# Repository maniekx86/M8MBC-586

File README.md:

# M8MBC-586

Open-source Pentium motherboard with an FPGA chipset - hardware repository

Work in progress...

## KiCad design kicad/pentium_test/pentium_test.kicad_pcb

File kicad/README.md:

# M8MBC-586 KiCad source

KiCad schematics and PCB design of the M8MBC-586 project. Not production ready (as time of writing the design is being checked)

## Credits
- Socket 7 symbol & footprint - Rigo (0xCats) - https://github.com/rigred/kicad-retro/
- CPU VRM - Necroware - https://github.com/necroware/s7-vrm

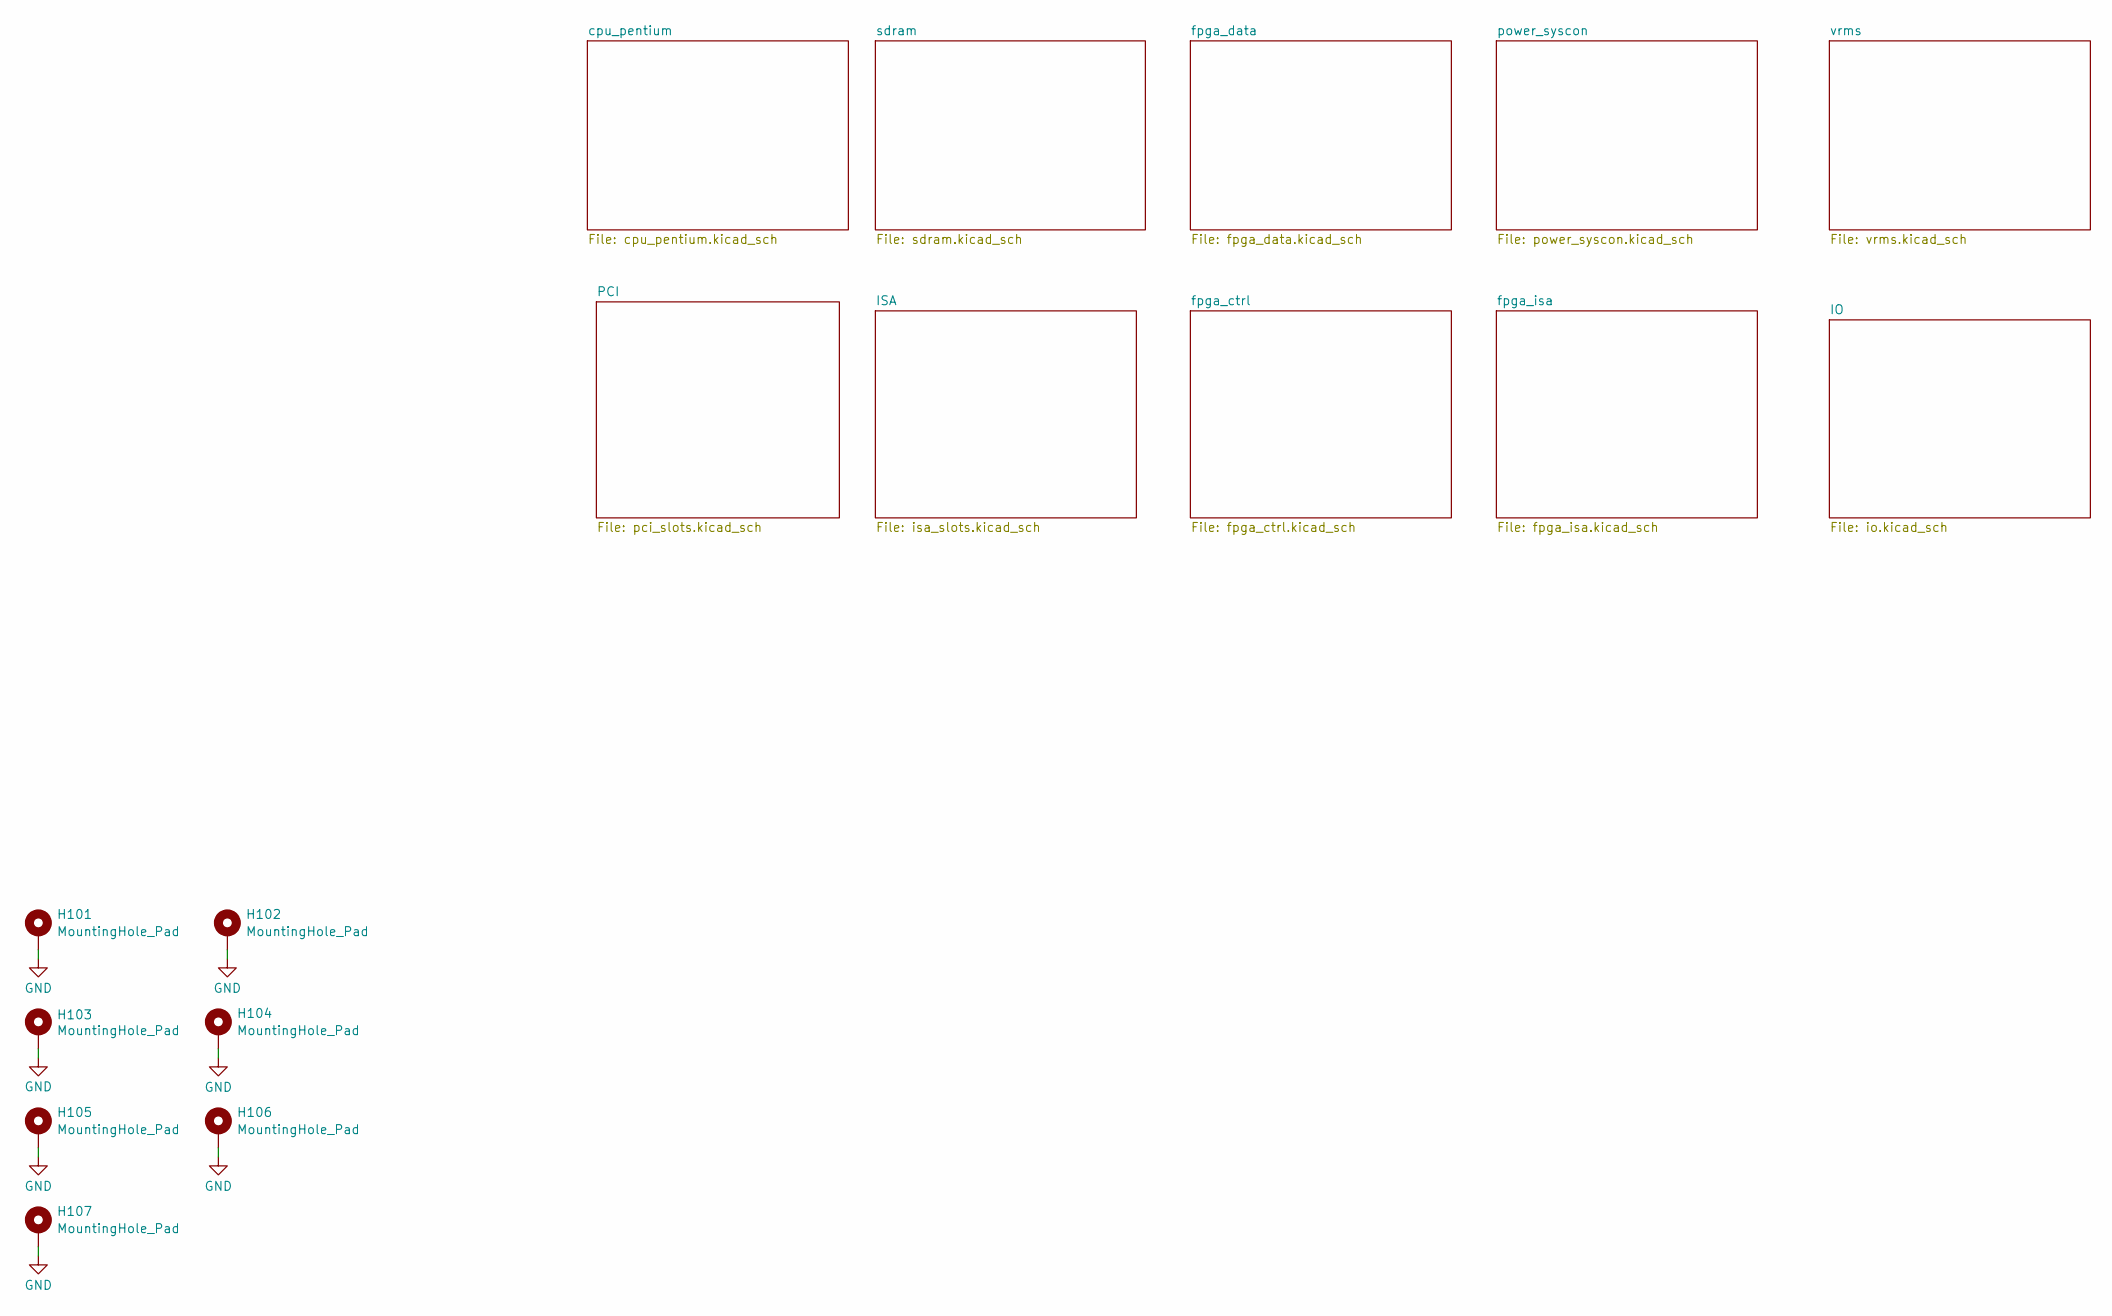
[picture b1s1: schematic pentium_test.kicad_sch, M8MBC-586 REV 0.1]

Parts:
H101, H102, H103, H104, H105, H106, H107: MountingHole_Pad; MountingHole_4.3mm_M4_Pad_Via

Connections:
GND: H101.1, H102.1, H103.1, H104.1, H105.1, H106.1, H107.1; also elsewhere on the board

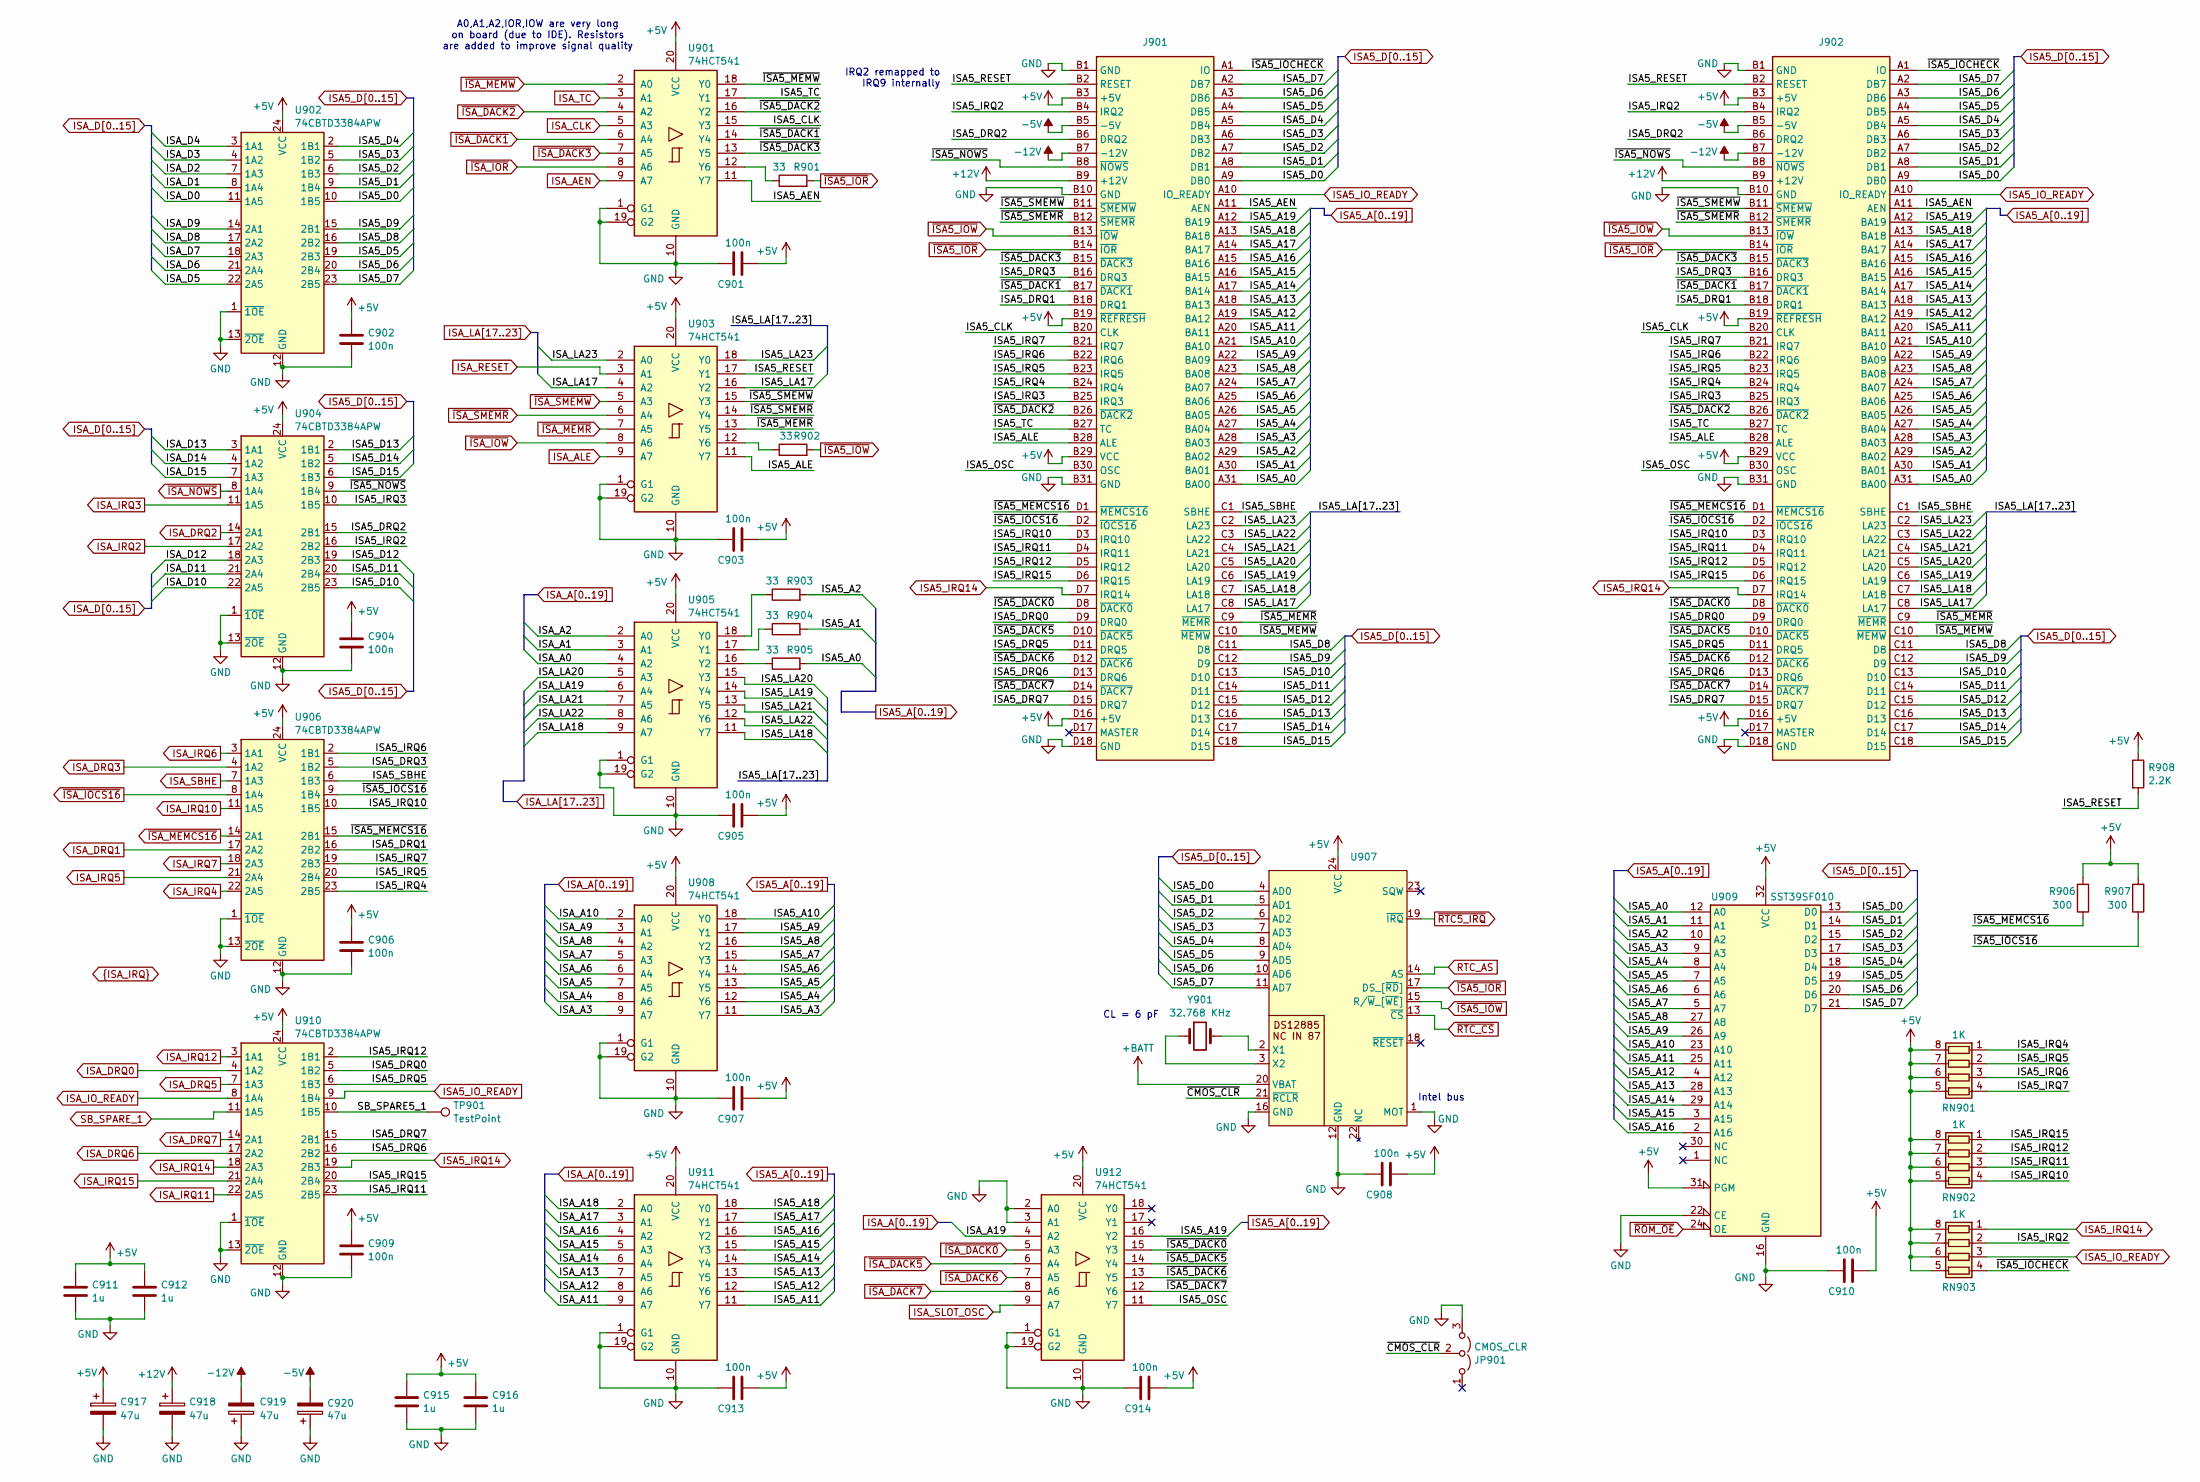
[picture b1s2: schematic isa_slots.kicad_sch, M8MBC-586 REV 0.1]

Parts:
C901, C902, C903, C904, C905, C906, C907, C908, C909, C910, C913, C914: 100n; C_0603_1608Metric
C911, C912, C915, C916: 1u; C_0805_2012Metric
C917, C918, C919, C920: 47u; CP_Radial_D5.0mm_P2.50mm
J901, J902: TE_7-5530843-0
JP901: CMOS_CLR; PinHeader_1x03_P2.54mm_Vertical
R901, R902, R903, R904, R905: 33; R_0603_1608Metric
R906, R907: 300; R_0603_1608Metric
R908: 2.2K; R_0603_1608Metric
RN901, RN902, RN903: 1K; R_Array_Convex_4x0603
TP901: TestPoint; TestPoint_Pad_D1.0mm
U901, U903, U905, U908, U911, U912: 74HCT541; TSSOP-20_4.4x6.5mm_P0.65mm
U902, U904, U906, U910: 74CBTD3384APW; TSSOP-24_4.4x7.8mm_P0.65mm
U907: DIP-24_W15.24mm_Socket
U909: SST39SF010; DIP-32_W15.24mm_Socket
Y901: 32.768 KHz; Crystal_C38-LF_D3.0mm_L8.0mm_Horizontal

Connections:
+5V: C901.2, C902.1, C903.2, C904.1, C905.2, C906.1, C907.2, C908.2, C909.1, C910.2, C911.1, C912.1, C913.2, C914.2, C915.1, C916.1, C917.1, J901.B3 (+5V), J901.B19 (~REFRESH), J901.B29 (VCC), J901.D16 (+5V), J902.B3 (+5V), J902.B19 (~REFRESH), J902.B29 (VCC), J902.D16 (+5V), R906.2, R907.2, R908.1, RN901.5 (R4.2), RN901.6 (R3.2), RN901.7 (R2.2), RN901.8 (R1.2), RN902.5 (R4.2), RN902.6 (R3.2), RN902.7 (R2.2), RN902.8 (R1.2), RN903.5 (R4.2), RN903.6 (R3.2), RN903.7 (R2.2), RN903.8 (R1.2), U901.20 (VCC), U902.24 (VCC), U903.20 (VCC), U904.24 (VCC), U905.20 (VCC), U906.24 (VCC), U907.24 (VCC), U908.20 (VCC), U909.31 (PGM), U909.32 (VCC), U910.24 (VCC), U911.20 (VCC), U912.20 (VCC); also elsewhere on the board
+12V: C918.1, J901.B9 (+12V), J902.B9 (+12V); also elsewhere on the board
+BATT: U907.20 (VBAT); also elsewhere on the board
-5V: C920.2, J901.B5 (-5V), J902.B5 (-5V); also elsewhere on the board
-12V: C919.2, J901.B7 (-12V), J902.B7 (-12V); also elsewhere on the board
/ISA/ISA5_AEN: J901.A11 (AEN), J902.A11 (AEN), U901.11 (Y7)
/ISA/ISA5_ALE: J901.B28 (ALE), J902.B28 (ALE), U903.11 (Y7)
/ISA/ISA5_CLK: J901.B20 (CLK), J902.B20 (CLK), U901.15 (Y3)
/ISA/ISA5_DRQ0: J901.D9 (DRQ0), J902.D9 (DRQ0), U910.5 (1B2)
/ISA/ISA5_DRQ1: J901.B18 (DRQ1), J902.B18 (DRQ1), U906.16 (2B2)
/ISA/ISA5_DRQ2: J901.B6 (DRQ2), J902.B6 (DRQ2), U904.15 (2B1)
/ISA/ISA5_DRQ3: J901.B16 (DRQ3), J902.B16 (DRQ3), U906.5 (1B2)
/ISA/ISA5_DRQ5: J901.D11 (DRQ5), J902.D11 (DRQ5), U910.6 (1B3)
/ISA/ISA5_DRQ6: J901.D13 (DRQ6), J902.D13 (DRQ6), U910.16 (2B2)
/ISA/ISA5_DRQ7: J901.D15 (DRQ7), J902.D15 (DRQ7), U910.15 (2B1)
/ISA/ISA5_IRQ2: J901.B4 (IRQ2), J902.B4 (IRQ2), RN903.2 (R2.1), U904.16 (2B2)
/ISA/ISA5_IRQ3: J901.B25 (IRQ3), J902.B25 (IRQ3), U904.10 (1B5)
/ISA/ISA5_IRQ4: J901.B24 (IRQ4), J902.B24 (IRQ4), RN901.1 (R1.1), U906.23 (2B5)
/ISA/ISA5_IRQ5: J901.B23 (IRQ5), J902.B23 (IRQ5), RN901.2 (R2.1), U906.20 (2B4)
/ISA/ISA5_IRQ6: J901.B22 (IRQ6), J902.B22 (IRQ6), RN901.3 (R3.1), U906.2 (1B1)
/ISA/ISA5_IRQ7: J901.B21 (IRQ7), J902.B21 (IRQ7), RN901.4 (R4.1), U906.19 (2B3)
/ISA/ISA5_IRQ10: J901.D3 (IRQ10), J902.D3 (IRQ10), RN902.4 (R4.1), U906.10 (1B5)
/ISA/ISA5_IRQ11: J901.D4 (IRQ11), J902.D4 (IRQ11), RN902.3 (R3.1), U910.23 (2B5)
/ISA/ISA5_IRQ12: J901.D5 (IRQ12), J902.D5 (IRQ12), RN902.2 (R2.1), U910.2 (1B1)
/ISA/ISA5_IRQ15: J901.D6 (IRQ15), J902.D6 (IRQ15), RN902.1 (R1.1), U910.20 (2B4)
/ISA/ISA5_LA17: J901.C8 (LA17), J902.C8 (LA17), U903.16 (Y2)
/ISA/ISA5_LA18: J901.C7 (LA18), J902.C7 (LA18), U905.11 (Y7)
/ISA/ISA5_LA19: J901.C6 (LA19), J902.C6 (LA19), U905.14 (Y4)
/ISA/ISA5_LA20: J901.C5 (LA20), J902.C5 (LA20), U905.15 (Y3)
/ISA/ISA5_LA21: J901.C4 (LA21), J902.C4 (LA21), U905.13 (Y5)
/ISA/ISA5_LA22: J901.C3 (LA22), J902.C3 (LA22), U905.12 (Y6)
/ISA/ISA5_LA23: J901.C2 (LA23), J902.C2 (LA23), U903.18 (Y0)
/ISA/ISA5_OSC: J901.B30 (OSC), J902.B30 (OSC), U912.11 (Y7)
/ISA/ISA5_RESET: J901.B2 (RESET), J902.B2 (RESET), R908.2, U903.17 (Y1)
/ISA/ISA5_SBHE: J901.C1 (SBHE), J902.C1 (SBHE), U906.6 (1B3)
/ISA/ISA5_TC: J901.B27 (TC), J902.B27 (TC), U901.17 (Y1)
/ISA/SB_SPARE5_1: TP901.1, U910.10 (1B5)
/ISA/~CMOS_CLR: JP901.2 (C), U907.21 (~RCLR)
/ISA/~ISA5_DACK0: J901.D8 (~DACK0), J902.D8 (~DACK0), U912.15 (Y3)
/ISA/~ISA5_DACK1: J901.B17 (~DACK1), J902.B17 (~DACK1), U901.14 (Y4)
/ISA/~ISA5_DACK2: J901.B26 (~DACK2), J902.B26 (~DACK2), U901.16 (Y2)
/ISA/~ISA5_DACK3: J901.B15 (~DACK3), J902.B15 (~DACK3), U901.13 (Y5)
/ISA/~ISA5_DACK5: J901.D10 (~DACK5), J902.D10 (~DACK5), U912.14 (Y4)
/ISA/~ISA5_DACK6: J901.D12 (~DACK6), J902.D12 (~DACK6), U912.13 (Y5)
/ISA/~ISA5_DACK7: J901.D14 (~DACK7), J902.D14 (~DACK7), U912.12 (Y6)
/ISA/~ISA5_IOCHECK: J901.A1 (IO), J902.A1 (IO), RN903.4 (R4.1)
/ISA/~ISA5_IOCS16: J901.D2 (~IOCS16), J902.D2 (~IOCS16), R907.1, U906.9 (1B4)
/ISA/~ISA5_MEMCS16: J901.D1 (~MEMCS16), J902.D1 (~MEMCS16), R906.1, U906.15 (2B1)
/ISA/~ISA5_MEMR: J901.C9 (~MEMR), J902.C9 (~MEMR), U903.13 (Y5)
/ISA/~ISA5_MEMW: J901.C10 (~MEMW), J902.C10 (~MEMW), U901.18 (Y0)
/ISA/~ISA5_NOWS: J901.B8 (~NOWS), J902.B8 (~NOWS), U904.9 (1B4)
/ISA/~ISA5_SMEMR: J901.B12 (~SMEMR), J902.B12 (~SMEMR), U903.14 (Y4)
/ISA/~ISA5_SMEMW: J901.B11 (~SMEMW), J902.B11 (~SMEMW), U903.15 (Y3)
GND: C901.1, C902.2, C903.1, C904.2, C905.1, C906.2, C907.1, C908.1, C909.2, C910.1, C911.2, C912.2, C913.1, C914.1, C915.2, C916.2, C917.2, C918.2, C919.1, C920.1, J901.B1 (GND), J901.B10 (GND), J901.B31 (GND), J901.D18 (GND), J902.B1 (GND), J902.B10 (GND), J902.B31 (GND), J902.D18 (GND), JP901.3 (B), U901.1 (G1), U901.10 (GND), U901.19 (G2), U902.1 (~1OE), U902.12 (GND), U902.13 (~2OE), U903.1 (G1), U903.10 (GND), U903.19 (G2), U904.1 (~1OE), U904.12 (GND), U904.13 (~2OE), U905.1 (G1), U905.10 (GND), U905.19 (G2), U906.1 (~1OE), U906.12 (GND), U906.13 (~2OE), U907.1 (MOT), U907.12 (GND), U907.16 (GND), U908.1 (G1), U908.10 (GND), U908.19 (G2), U909.16 (GND), U909.22 (CE), U910.1 (~1OE), U910.12 (GND), U910.13 (~2OE), U911.1 (G1), U911.10 (GND), U911.19 (G2), U912.1 (G1), U912.2 (A0), U912.3 (A1), U912.10 (GND), U912.19 (G2); also elsewhere on the board
ISA5_A0: J901.A31 (BA00), J902.A31 (BA00), R905.2, U909.12 (A0); also elsewhere on the board
ISA5_A1: J901.A30 (BA01), J902.A30 (BA01), R904.2, U909.11 (A1); also elsewhere on the board
ISA5_A2: J901.A29 (BA02), J902.A29 (BA02), R903.2, U909.10 (A2); also elsewhere on the board
ISA5_A3: J901.A28 (BA03), J902.A28 (BA03), U908.11 (Y7), U909.9 (A3)
ISA5_A4: J901.A27 (BA04), J902.A27 (BA04), U908.12 (Y6), U909.8 (A4)
ISA5_A5: J901.A26 (BA05), J902.A26 (BA05), U908.13 (Y5), U909.7 (A5)
ISA5_A6: J901.A25 (BA06), J902.A25 (BA06), U908.14 (Y4), U909.6 (A6)
ISA5_A7: J901.A24 (BA07), J902.A24 (BA07), U908.15 (Y3), U909.5 (A7)
ISA5_A8: J901.A23 (BA08), J902.A23 (BA08), U908.16 (Y2), U909.27 (A8)
ISA5_A9: J901.A22 (BA09), J902.A22 (BA09), U908.17 (Y1), U909.26 (A9)
ISA5_A10: J901.A21 (BA10), J902.A21 (BA10), U908.18 (Y0), U909.23 (A10)
ISA5_A11: J901.A20 (BA11), J902.A20 (BA11), U909.25 (A11), U911.11 (Y7)
ISA5_A12: J901.A19 (BA12), J902.A19 (BA12), U909.4 (A12), U911.12 (Y6)
ISA5_A13: J901.A18 (BA13), J902.A18 (BA13), U909.28 (A13), U911.13 (Y5)
ISA5_A14: J901.A17 (BA14), J902.A17 (BA14), U909.29 (A14), U911.14 (Y4)
ISA5_A15: J901.A16 (BA15), J902.A16 (BA15), U909.3 (A15), U911.15 (Y3)
ISA5_A16: J901.A15 (BA16), J902.A15 (BA16), U909.2 (A16), U911.16 (Y2)
ISA5_A17: J901.A14 (BA17), J902.A14 (BA17), U911.17 (Y1)
ISA5_A18: J901.A13 (BA18), J902.A13 (BA18), U911.18 (Y0)
ISA5_A19: J901.A12 (BA19), J902.A12 (BA19), U912.16 (Y2)
ISA5_D0: J901.A9 (DB0), J902.A9 (DB0), U902.10 (1B5), U907.4 (AD0), U909.13 (D0)
ISA5_D1: J901.A8 (DB1), J902.A8 (DB1), U902.9 (1B4), U907.5 (AD1), U909.14 (D1)
ISA5_D2: J901.A7 (DB2), J902.A7 (DB2), U902.6 (1B3), U907.6 (AD2), U909.15 (D2)
ISA5_D3: J901.A6 (DB3), J902.A6 (DB3), U902.5 (1B2), U907.7 (AD3), U909.17 (D3)
ISA5_D4: J901.A5 (DB4), J902.A5 (DB4), U902.2 (1B1), U907.8 (AD4), U909.18 (D4)
ISA5_D5: J901.A4 (DB5), J902.A4 (DB5), U902.19 (2B3), U907.9 (AD5), U909.19 (D5)
ISA5_D6: J901.A3 (DB6), J902.A3 (DB6), U902.20 (2B4), U907.10 (AD6), U909.20 (D6)
ISA5_D7: J901.A2 (DB7), J902.A2 (DB7), U902.23 (2B5), U907.11 (AD7), U909.21 (D7)
ISA5_D8: J901.C11 (D8), J902.C11 (D8), U902.16 (2B2)
ISA5_D9: J901.C12 (D9), J902.C12 (D9), U902.15 (2B1)
ISA5_D10: J901.C13 (D10), J902.C13 (D10), U904.23 (2B5)
ISA5_D11: J901.C14 (D11), J902.C14 (D11), U904.20 (2B4)
ISA5_D12: J901.C15 (D12), J902.C15 (D12), U904.19 (2B3)
ISA5_D13: J901.C16 (D13), J902.C16 (D13), U904.2 (1B1)
ISA5_D14: J901.C17 (D14), J902.C17 (D14), U904.5 (1B2)
ISA5_D15: J901.C18 (D15), J902.C18 (D15), U904.6 (1B3)
ISA5_IO_READY: J901.A10 (IO_READY), J902.A10 (IO_READY), RN903.3 (R3.1), U910.9 (1B4); also elsewhere on the board
ISA5_IRQ14: J901.D7 (IRQ14), J902.D7 (IRQ14), RN903.1 (R1.1), U910.19 (2B3); also elsewhere on the board
ISA_A0: U905.4 (A2); also elsewhere on the board
ISA_A1: U905.3 (A1); also elsewhere on the board
ISA_A2: U905.2 (A0); also elsewhere on the board
ISA_A3: U908.9 (A7); also elsewhere on the board
ISA_A4: U908.8 (A6); also elsewhere on the board
ISA_A5: U908.7 (A5); also elsewhere on the board
ISA_A6: U908.6 (A4); also elsewhere on the board
ISA_A7: U908.5 (A3); also elsewhere on the board
ISA_A8: U908.4 (A2); also elsewhere on the board
ISA_A9: U908.3 (A1); also elsewhere on the board
ISA_A10: U908.2 (A0); also elsewhere on the board
ISA_A11: U911.9 (A7); also elsewhere on the board
ISA_A12: U911.8 (A6); also elsewhere on the board
ISA_A13: U911.7 (A5); also elsewhere on the board
ISA_A14: U911.6 (A4); also elsewhere on the board
ISA_A15: U911.5 (A3); also elsewhere on the board
ISA_A16: U911.4 (A2); also elsewhere on the board
ISA_A17: U911.3 (A1); also elsewhere on the board
ISA_A18: U911.2 (A0); also elsewhere on the board
ISA_A19: U912.4 (A2); also elsewhere on the board
ISA_AEN: U901.9 (A7); also elsewhere on the board
ISA_ALE: U903.9 (A7); also elsewhere on the board
ISA_CLK: U901.5 (A3); also elsewhere on the board
ISA_D0: U902.11 (1A5); also elsewhere on the board
ISA_D1: U902.8 (1A4); also elsewhere on the board
ISA_D2: U902.7 (1A3); also elsewhere on the board
ISA_D3: U902.4 (1A2); also elsewhere on the board
ISA_D4: U902.3 (1A1); also elsewhere on the board
ISA_D5: U902.22 (2A5); also elsewhere on the board
ISA_D6: U902.21 (2A4); also elsewhere on the board
ISA_D7: U902.18 (2A3); also elsewhere on the board
ISA_D8: U902.17 (2A2); also elsewhere on the board
ISA_D9: U902.14 (2A1); also elsewhere on the board
ISA_D10: U904.22 (2A5); also elsewhere on the board
ISA_D11: U904.21 (2A4); also elsewhere on the board
ISA_D12: U904.18 (2A3); also elsewhere on the board
ISA_D13: U904.3 (1A1); also elsewhere on the board
ISA_D14: U904.4 (1A2); also elsewhere on the board
ISA_D15: U904.7 (1A3); also elsewhere on the board
ISA_DRQ0: U910.4 (1A2); also elsewhere on the board
ISA_DRQ1: U906.17 (2A2); also elsewhere on the board
ISA_DRQ2: U904.14 (2A1); also elsewhere on the board
ISA_DRQ3: U906.4 (1A2); also elsewhere on the board
ISA_DRQ5: U910.7 (1A3); also elsewhere on the board
ISA_DRQ6: U910.17 (2A2); also elsewhere on the board
ISA_DRQ7: U910.14 (2A1); also elsewhere on the board
ISA_IO_READY: U910.8 (1A4); also elsewhere on the board
ISA_IRQ2: U904.17 (2A2); also elsewhere on the board
ISA_IRQ3: U904.11 (1A5); also elsewhere on the board
ISA_IRQ4: U906.22 (2A5); also elsewhere on the board
ISA_IRQ5: U906.21 (2A4); also elsewhere on the board
ISA_IRQ6: U906.3 (1A1); also elsewhere on the board
ISA_IRQ7: U906.18 (2A3); also elsewhere on the board
ISA_IRQ10: U906.11 (1A5); also elsewhere on the board
ISA_IRQ11: U910.22 (2A5); also elsewhere on the board
ISA_IRQ12: U910.3 (1A1); also elsewhere on the board
ISA_IRQ14: U910.18 (2A3); also elsewhere on the board
ISA_IRQ15: U910.21 (2A4); also elsewhere on the board
ISA_LA17: U903.4 (A2); also elsewhere on the board
ISA_LA18: U905.9 (A7); also elsewhere on the board
ISA_LA19: U905.6 (A4); also elsewhere on the board
ISA_LA20: U905.5 (A3); also elsewhere on the board
ISA_LA21: U905.7 (A5); also elsewhere on the board
ISA_LA22: U905.8 (A6); also elsewhere on the board
ISA_LA23: U903.2 (A0); also elsewhere on the board
ISA_RESET: U903.3 (A1); also elsewhere on the board
ISA_SBHE: U906.7 (1A3); also elsewhere on the board
ISA_SLOT_OSC: U912.9 (A7); also elsewhere on the board
ISA_TC: U901.3 (A1); also elsewhere on the board
unnamed: R901.1, U901.12 (Y6)
unnamed: R902.1, U903.12 (Y6)
unnamed: R903.1, U905.18 (Y0)
unnamed: R904.1, U905.17 (Y1)
unnamed: R905.1, U905.16 (Y2)
unnamed: U907.2 (X1), Y901.2
unnamed: U907.3 (X2), Y901.1
RTC_AS: U907.14 (AS); also elsewhere on the board
SB_SPARE_1: U910.11 (1A5); also elsewhere on the board
~ISA5_IOR: J901.B14 (~IOR), J902.B14 (~IOR), R901.2, U907.17 (DS_[~RD]); also elsewhere on the board
~ISA5_IOW: J901.B13 (~IOW), J902.B13 (~IOW), R902.2, U907.15 (R/~W_[~WE]); also elsewhere on the board
~ISA_DACK0: U912.5 (A3); also elsewhere on the board
~ISA_DACK1: U901.6 (A4); also elsewhere on the board
~ISA_DACK2: U901.4 (A2); also elsewhere on the board
~ISA_DACK3: U901.7 (A5); also elsewhere on the board
~ISA_DACK5: U912.6 (A4); also elsewhere on the board
~ISA_DACK6: U912.7 (A5); also elsewhere on the board
~ISA_DACK7: U912.8 (A6); also elsewhere on the board
~ISA_IOCS16: U906.8 (1A4); also elsewhere on the board
~ISA_IOR: U901.8 (A6); also elsewhere on the board
~ISA_IOW: U903.8 (A6); also elsewhere on the board
~ISA_MEMCS16: U906.14 (2A1); also elsewhere on the board
~ISA_MEMR: U903.7 (A5); also elsewhere on the board
~ISA_MEMW: U901.2 (A0); also elsewhere on the board
~ISA_NOWS: U904.8 (1A4); also elsewhere on the board
~ISA_SMEMR: U903.6 (A4); also elsewhere on the board
~ISA_SMEMW: U903.5 (A3); also elsewhere on the board
~ROM_OE: U909.24 (OE); also elsewhere on the board
~RTC5_IRQ: U907.19 (~IRQ); also elsewhere on the board
~RTC_CS: U907.13 (~CS); also elsewhere on the board

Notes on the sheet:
IRQ2 remapped to IRQ9 internally
Intel bus
A0,A1,A2,IOR,IOW are very long on board (due to IDE). Resistors are added to improve signal quality
CL = 6 pF
